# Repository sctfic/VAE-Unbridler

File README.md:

# E-BikeCockpit — télémétrie et simulateur d'impulsions

Version Android **0.4.20** — auteur **Lopez Alban**.

Le panneau DEBUG de la carte détaille les étapes et durées de chargement.
Voir [le chargement et les caches 3D](MAP_LOADING.md) et [les changements 0.4.20](RELEASE_0.4.20.md).

Un appui long sur la scène 3D ouvre les options d'affichage : lignes de niveau,
cours d'eau, routes, chemins et bâtiments. Les choix sont mémorisés localement.
Les bâtiments sont représentés par leurs contours au sol (ways OpenStreetMap),
sans hauteur inventée ; toutes les couches cochées restent affichées en vue d'ensemble.
Les données OSM enrichies utilisent un cache v2 :
le premier chargement peut nécessiter Internet, les suivants réutilisent le cache.
Les couches OSM partagent leur cache. L'option cadastre charge séparément les
parcelles IGN/DGFiP proches du GPS et affiche leur section et numéro (pas les
propriétaires). Ces données sont ensuite conservées en cache local.

Le projet contient deux sous-projets indépendants :

- `firmware-esp32/` : firmware ESP-IDF pour ESP32-S3 Zero. Le contact magnétique de roue est lu sur GPIO 5. Le générateur d'impulsions moteur fonctionne sur GPIO 6 dans une tâche temps réel séparée de Bluetooth.
- `android-app/` : application Android native, tableau de bord plein écran et service persistant Bluetooth/GPS.

Le protocole commun est documenté dans [`BLE_PROTOCOL.md`](BLE_PROTOCOL.md) et le câblage dans [`firmware-esp32/HARDWARE.md`](firmware-esp32/HARDWARE.md).

## Fonctions disponibles

Le [cockpit holographique](COCKPIT.md) affiche les grandes valeurs sur une scène 3D native,
avec relief réel filaire, courbes de niveau, cadrage automatique et historique local du trajet.

- vitesse GPS principale animée, vitesse de roue et vitesse transmise au moteur ;
- profil d'altitude 500 m / complet / 2 km (un toucher pour changer) et pente par régression sur les 10 derniers points GPS valides en déplacement (3 à 30 réglables) ; l’axe horizontal suit la distance GPS validée, profil et pente figés à l’arrêt ;
- distance et trace GPS 3D orientée selon les derniers points ;
- GPS, altitude et tracé actifs dès l’ouverture de l’application, même sans ESP32 ;
- circonférence de roue ou diamètre réglable depuis l'application et enregistré dans l'ESP32 ;
- maintien de l'écran allumé et verrou CPU pendant le suivi GPS, indépendamment du Bluetooth ;
- association initiale avec l'ESP32, puis détection automatique de sa présence sur Android 12 ou plus récent.

## Sécurité électrique importante

### Modes Standard / Turbo

Un double toucher dans la zone des vitesses (hors boutons de réglage) bascule le mode
si l’ESP32 est connecté et dispose du firmware compatible. **Standard** (halo et anneau
bleus) transmet les impulsions au rythme réel ; **Turbo** (rouges) active la simulation
au-dessus du seuil configuré. Le nom est affiché dans le cadran et confirmé par la
télémétrie, indépendamment de la vitesse instantanée. Sans connexion, le mode est inconnu.
L’ESP32 démarre toujours en Standard ; une déconnexion Bluetooth conserve le mode en cours.
Les deux logiciels doivent être mis à jour. Vérifier les transitions sur banc, à l’arrêt,
avant utilisation ; le double toucher peut aussi être reconnu en roulant.

GPIO 6 est une sortie à drain ouvert : impulsion à 0 (signal relié à la masse), repos à 1 (haute impédance). Ce firmware concerne la carte ESP32-S3 Zero actuelle avec Bluetooth Standard/Turbo, pas une nouvelle carte.

La liaison directe suppose une entrée moteur à rappel 3,3 V compatible, une masse de signal commune et un courant limité. Une mesure à 3,3 V à vide ne valide pas à elle seule les transitoires ni le comportement ESP32 éteint. **Ne jamais court-circuiter VCC avec GND.** Voir les conditions et les tests dans [`firmware-esp32/HARDWARE.md`](firmware-esp32/HARDWARE.md).

## Installer l'application Android

### Diagnostic GPS et journal local

La grande vitesse privilégie le GPS valide ou estimé (effet glitch), puis la roue si le Bluetooth est connecté
(libellé **ROUE**), sinon affiche un tiret. Une vitesse roue positive et cohérente prend la priorité sur un zéro GPS valide.
Le bas du cadran affiche fournisseur, précision horizontale, âge de la mesure,
vitesse brute, incertitude de vitesse et décision du filtre. Sans mesures, il affiche
l’état de la localisation système et le temps depuis le dernier retour du fournisseur.

Le journal privé `files/gps-logs/gps-current.log` conserve ces diagnostics, les erreurs
d’abonnement et les démarrages/arrêts ; horodatages Unix en millisecondes, aucune
latitude/longitude. Écriture en arrière-plan, rotation à 4 Mio et deux archives
(`gps-1.log`, `gps-2.log`) : environ 12 Mio maximum. Les plus anciens événements
sont remplacés ; une surcharge extrême peut perdre des lignes. Les logs survivent
au redémarrage et à une mise à jour, mais pas à la désinstallation/effacement des données.

Depuis la 0.4.18, ce même journal conserve chaque télémétrie BLE reçue : séquence,
temps de fonctionnement de l'ESP32, périodes roue/moteur, vitesses, compteurs de
tours et d'impulsions, circonférence et mode. La vitesse GPS et sa validité sont
ajoutées pour comparer les mesures au même instant, sans coordonnées. Les étapes
de connexion BLE sont également conservées. Les anciennes versions ne permettaient
pas de diagnostiquer une perte d'impulsions à partir du seul journal GPS.

Avec le firmware correspondant, les lignes `SENSOR` ajoutent `rawIntervalUs`
(dernier intervalle brut entre fronts descendants GPIO 5, avant filtrage),
`edges`, `rejectedEdges` et `queueDroppedEdges`. Les lignes `BLE` indiquent
`wheelUs` (intervalle retenu) et `motorUs` (intervalle commandé), en microsecondes.
Les diagnostics bruts sont des instantanés à 5 Hz ; ils ne constituent pas une
trace exhaustive de tous les fronts. Les numéros `seq` associent les deux lignes.

Le [correctif Hardware v1 / app 0.4.18](RELEASE_0.4.18.md) décrit les limites du
diagnostic et les essais à effectuer sur le vélo.

Au prochain branchement USB avec débogage autorisé, récupérer chaque fichier présent
avec la version debug installée, sans réinstaller/effacer l’application :

```powershell
adb shell run-as com.alban.ebike ls files/gps-logs
adb exec-out run-as com.alban.ebike cat files/gps-logs/gps-current.log > gps-current.log
adb exec-out run-as com.alban.ebike cat files/gps-logs/gps-1.log > gps-1.log
adb exec-out run-as com.alban.ebike cat files/gps-logs/gps-2.log > gps-2.log
```

Les archives n’existent qu’après rotation. Ces fichiers restent locaux, sans envoi réseau.

1. Ouvrir le dossier `android-app` dans Android Studio et attendre la fin de la synchronisation Gradle.
2. Activer les options développeur et le débogage USB sur le téléphone, puis le brancher.
3. Choisir le téléphone dans la barre supérieure d'Android Studio et cliquer sur **Run**.
4. Au premier lancement, accepter Bluetooth, localisation, notifications et la localisation « Toujours autoriser ».
5. Allumer l'ESP32, toucher **ESP32** une seule fois dans l'application, puis confirmer l'association proposée par Android.

Le GPS démarre à l’ouverture de l’application une fois la localisation précise autorisée. L’altitude, le profil, la distance et le tracé continuent sans ESP32 et lors d’une déconnexion Bluetooth. Seules les vitesses de roue et moteur dépendent de la carte. La notification persistante permet d’arrêter le suivi. Les points peu précis (plus de 20 m d’incertitude) sont ignorés ; à l’intérieur, il peut être nécessaire de sortir pour obtenir un tracé. Une altitude absente n’est pas affichée comme une altitude mesurée de zéro.

Le bouton **ESP32** est gris hors connexion et cyan gras lorsqu’il est connecté. La vitesse GPS privilégie la mesure native Android. En son absence ou si elle est refusée, une régression pondérée des coordonnées sur les six dernières secondes fournit une estimation signalée par des bandes de chiffres décalées aléatoirement. Trois positions sur au moins deux secondes sont nécessaires ; les positions périmées, imprécises ou incohérentes restent rejetées. Le départ demande trois mesures sur au moins 1,5 seconde et un déplacement supérieur à l’incertitude cumulée. L’incertitude maximale vaut 1 m/s au départ, puis 30 % de la vitesse (bornée entre 1 et 3 m/s) en mouvement. Une médiane de trois mesures et un filtre exponentiel court atténuent les pics. Un arrêt bien mesuré remet immédiatement le filtre à zéro ; les petites vitesses ambiguës demandent deux mesures consécutives. Ces seuils peuvent masquer les déplacements très lents.

Une vitesse temporairement incertaine est maintenue au maximum deux secondes, avec la mention **maintien** dans le diagnostic, puis utilise la régression positionnelle (repli roue connectée si aucune estimation, sinon **—**). Sans nouveau fix, le délai de péremption reste de quatre secondes. La trace et la distance sont validées séparément : des positions cohérentes continuent le parcours même sans vitesse native fiable. Un déplacement positionnel doit dépasser l’incertitude sur une fenêtre bornée ; un arrêt confirmé fige la distance. Seuls une perte de positions de plus de quatre secondes, un point invalide ou un saut excessif créent une interruption. Le journal GPS indique désormais `trace`, `append`, `segmentStart` et `stepM` pour diagnostiquer chaque décision. Ce filtre ne remplace pas un essai réel à l’extérieur.

Après association, la présence de l’ESP32 peut aussi démarrer le service ; pour ce démarrage en arrière-plan, accorder la localisation « Toujours autoriser ». Android peut empêcher une application d'ouvrir une fenêtre depuis l'arrière-plan selon la version du système ou le fabricant ; dans ce cas, la notification persistante **E-Bike** ouvre le tableau de bord en un toucher.

APK déjà construit : `android-app/app/build/outputs/apk/debug/app-debug.apk`.

### Ouverture automatique au démarrage de l’ESP32

Sur Android 12+, confirmer une fois l’association système proposée par E-Bike (ou toucher **ESP32** pour la relancer). Une connexion BLE directe ne suffit pas : l’association doit être enregistrée par Android. Durant cette étape, l’application libère sa connexion pour que la carte soit visible dans la recherche système.

Quand la carte réapparaît, Android réveille le service compagnon ; celui-ci demande l’ouverture du tableau de bord si l’écran est allumé et déverrouillé. Le mode plein écran est réappliqué lorsque la fenêtre revient au premier plan. Le service reste actif si la tâche est retirée des applications récentes. Le téléphone et l’ESP32 n’ont pas besoin d’être branchés ensemble au PC : la carte doit simplement être alimentée.

Un **Forcer l’arrêt** dans les paramètres Android peut bloquer le réveil jusqu’à la prochaine ouverture manuelle. Les restrictions d’arrière-plan propres au fabricant peuvent également intervenir ; vérifier ce fonctionnement sur le téléphone réel après association. La notification reste accessible si le système refuse le lancement de la fenêtre. Aucun contournement de l’écran de verrouillage ni autorisation de superposition n’est utilisé.

Quand le téléphone est verrouillé ou son écran éteint, la détection de présence (ou une nouvelle connexion BLE) publie une notification **« Votre vélo est prêt »**, avec le bouton **« Ouvrir E-Bike »**. Elle utilise le canal **ESP32 à proximité**, distinct de la notification silencieuse du suivi GPS. Un même identifiant évite l’empilement des alertes et les mises à jour n’émettent pas une seconde alerte. L’invitation disparaît à l’ouverture de l’application, à la déconnexion ou à la disparition de la carte. Son affichage sur l’écran verrouillé et son signal sonore restent soumis aux réglages de notifications du téléphone. Si l’application ne tourne plus, l’association système décrite ci-dessus doit être active pour recevoir la détection de présence.

## Flasher l'ESP32-S3 Zero

Ouvrir **ESP-IDF PowerShell**, puis :

```powershell
cd "C:\Users\Alban\Desktop\Dev\www\E-Bike\firmware-esp32"
idf.py set-target esp32s3
idf.py build
idf.py -p COM4 flash monitor
```

Remplacer `COM4` par le port réellement attribué à la carte. Si l'envoi ne démarre pas : maintenir **BOOT**, brancher l'USB ou appuyer sur **RESET**, relâcher **BOOT**, puis relancer la dernière commande.

Firmware déjà construit : `firmware-esp32/build/ebike_firmware.bin`.

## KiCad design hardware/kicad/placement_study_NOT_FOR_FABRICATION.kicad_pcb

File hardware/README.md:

# E-Bike controller board

Compact ESP32-S3 controller for the E-BikeCockpit firmware.

## Frozen prototype requirements

- Maximum PCB outline: 30 mm x 20 mm.
- Maximum assembled height: 10 mm.
- Supply: Bosch eBike 12 V power port, only when that port is not already used by Bosch ABS.
- Programming: USB-C, including when the 12 V supply is absent.
- Field wiring: six plated through holes, arranged as three pairs:
  - `12V+`, `GND`
  - `WHEEL`, `GND`
  - `MOTOR_A`, `MOTOR_B`
- `WHEEL` is a local, dry reed contact to ground.
- `MOTOR_A` / `MOTOR_B` form a non-polarized isolated semiconductor contact.
- Indicators:
  - red: wheel input contact closed;
  - green: isolated output is being commanded closed;
  - blue: Bluetooth connection active.
- Prototype quantity: five assembled boards.
- Manufacturers to quote: JLCPCB and AISLER.

## Electrical architecture

1. `12V+` passes through a resettable fuse, reverse-polarity protection and a TVS clamp.
2. A fixed-output AP63203 buck regulator creates `3V3_AUX`.
3. USB VBUS feeds a 600 mA 3.3 V LDO and creates `3V3_USB`.
4. A TPS2116 power multiplexer is configured to select the higher 3.3 V
   input and block reverse current. USB is not guaranteed priority. Switchover
   continuity and reverse current remain to be verified on the prototype.
5. The ESP32-S3FH4R2 is powered from the selected 3.3 V rail.
6. USB D- and D+ connect to GPIO19 and GPIO20 through 22 ohm series resistors and low-capacitance ESD protection.
7. GPIO5 reads the protected wheel input. The red LED and its resistor are connected from 3.3 V to the input, so the LED lights when the dry contact closes.
8. GPIO6 drives the isolated MOS switch through a transistor and the green
   indicator through a separate current-limiting resistor.
9. GPIO21 drives the blue Bluetooth indicator using the firmware in this repository.

## Manufacturing outputs

The release directory must contain, after design validation:

- native KiCad schematic and PCB files;
- schematic PDF;
- Gerber and NC drill ZIP;
- BOM with manufacturer and supplier part numbers;
- CPL / pick-and-place file;
- top and bottom assembly drawings;
- STEP model;
- ERC, DRC and Gerber review reports;
- JLCPCB and AISLER quotation notes for five boards.

The detailed circuit capture specification is in `CIRCUIT_SPEC.md`. The live
parts and quotation procedure are in `SOURCING.md`.

`kicad/power_study.kicad_sch` is an incomplete study of the power section,
ESP32 pinout, reset, clock and wheel/isolated output interfaces, not a manufacturing schematic. Its
generic symbols have no verified footprints and all pins are passive, so an
ERC pass cannot validate the design. `power_study.kicad_pro`, `sym-lib-table`
and `draft.kicad_sym` make the provisional symbols available locally; they do
not make them electrically verified. Six debug test points are in the study
but have not been placed on the PCB. The USB data connector, decoupling,
wheel ESD protection and RF matching are captured provisionally; the RF
supply filter value, ESD protection and crystal pinout remain to be verified.
Do not use its netlist or preview to order a PCB.

`kicad/placement_study_NOT_FOR_FABRICATION.kicad_pcb` is a mechanical
placement experiment on a 30 x 20 mm four-layer 0.8 mm board. Only major
parts and six unconnected wire holes are placed; some footprints are only
approximations, the output switch and driver are on the bottom, and no tracks
are routed. Only the USB connector's GND and VBUS nets are assigned. The DRC
report covers placed objects only: it says nothing about missing components,
radio keep-out, circuit connectivity or production readiness.

## Prototype limitations

This revision integrates the bare ESP32-S3FH4R2 to meet the 30 mm x 20 mm outline. RF matching and antenna performance must be measured on the first assembled prototypes. The first order is therefore an engineering prototype, not a validated production design.

The Bosch 12 V power port must not be shared with a Bosch ABS unit. Verify polarity before soldering the two supply wires.

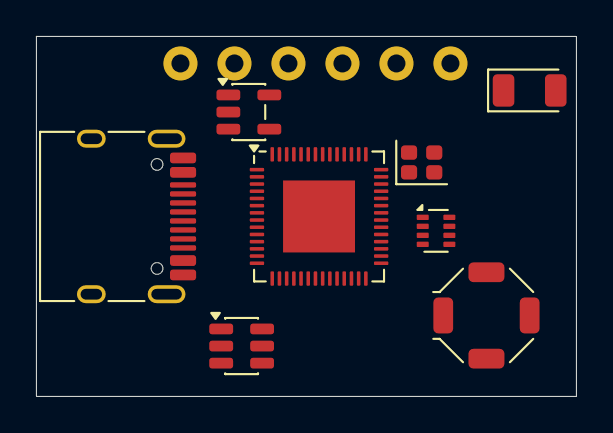
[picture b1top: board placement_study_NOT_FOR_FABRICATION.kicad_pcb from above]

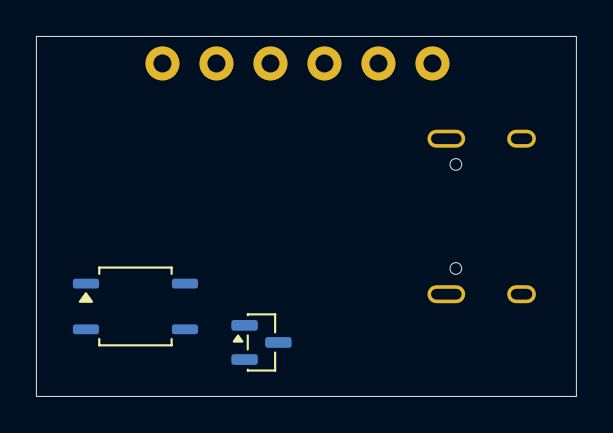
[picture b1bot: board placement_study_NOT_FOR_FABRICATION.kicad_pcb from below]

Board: 4 copper layers, 30.0 x 20.0 mm, 16 parts (2 on the bottom side), 2 nets, no tracks yet.

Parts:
AE1: 2450AT18A0100001E; Johanson_2450AT18x100_2400-2500Mhz
H1, H2, H3, H4, H5, H6: WIRE HOLE - NO NET
J1: TYPE-C-31-M-12; USB_C_Receptacle_HRO_TYPE-C-31-M-12
L1: 3.9uH - FOOTPRINT TO VERIFY; L_Bourns_SRU5016_5.2x5.2mm
Q1: MMBT3904; SOT-23
U1: ESP32-S3FH4R2; QFN-56-1EP_7x7mm_P0.4mm_EP4x4mm
U2: AP63203WU-7; TSOT-23-6
U3: AP2112K-3.3TRG1; SOT-23-5
U4: TPS2116DRLR; SOT-583-8
U5: AQY222R1SX - FOOTPRINT TO VERIFY; SOP-4_3.8x4.1mm_P2.54mm
Y1: 40MHz; Crystal_SMD_2016-4Pin_2.0x1.6mm

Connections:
GND: J1.A1, J1.A12, J1.B1, J1.B12, J1.SH
USB_VBUS: J1.A4, J1.A9, J1.B4, J1.B9

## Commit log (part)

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2024-07-07 first commit v0.1 (usable)
2024-08-09 feat (v1.0) : 0 to 24.1km/h
2024-09-09 feat(22.2):Rendering relative speed upper 22.2km/h
2024-09-09 feat(led): display real speed as led colors 10 to 50 is Green to Red
